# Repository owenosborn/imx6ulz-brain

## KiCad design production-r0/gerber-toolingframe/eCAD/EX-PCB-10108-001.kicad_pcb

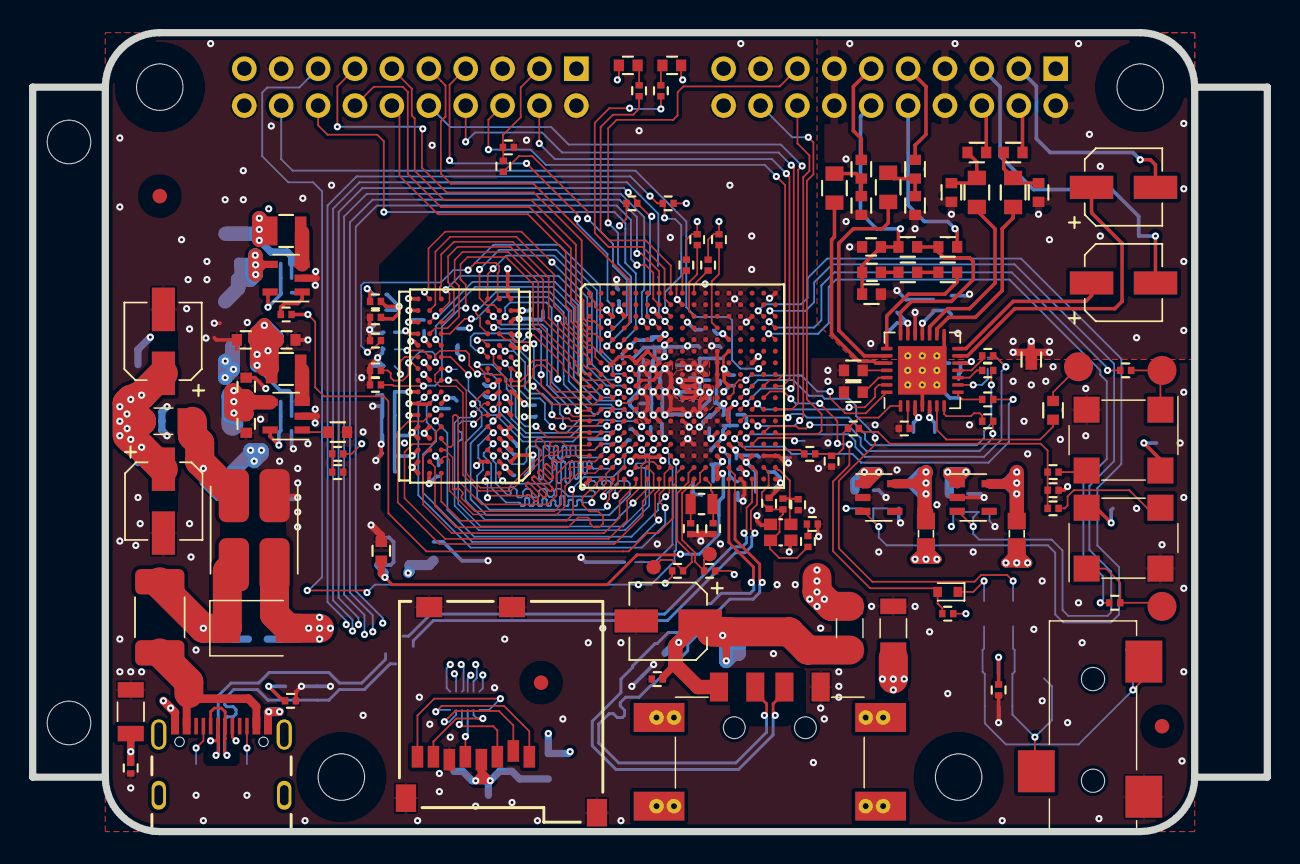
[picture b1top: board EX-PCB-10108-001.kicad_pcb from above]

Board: 4 copper layers, 85.0 x 55.0 mm, 248 parts (0 on the bottom side), 203 nets.

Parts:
C1, C4, C5, C7, C16, C21, C22, C25, C26, C27, C28, C31, C301, C314, C319, C407, C414, C520, C521, C701, C702, C707, C708, C709, C710: PV-EC-CAP-017-22U; 0603
C2, C3, C6, C46, C47: PV-EC-ALU-004-100U; 5.5x5.5x5
C10, C11: PV-EC-CAP-014-8P; 0402
C12, C13, C23, C30, C52, C54, C66, C705, C706: PV-EC-CAP-014-18P; 0402
C14, C15, C24, C302, C303: PV-EC-CAP-010-4U7; 0402
C17: PV-EC-CAP-022-10N; 0603
C18, C19, C65: PV-EC-CAP-022-220N; 0603
C20, C29, C32, C33, C34, C36, C38, C39, C44, C45, C50, C53, C57, C58, C59, C304, C305, C306, C307, C308, C309, C310, C311, C312, C315, C317, C318, C401, C402, C403, C406, C408, C409, C411, C415, C416, C417, C418, C419, C420, C421, C422, C423, C424, C425, C426, C427, C501, C503, C507, C509: PV-EC-CAP-011-220N; 0402
C35, C37, C42, C43, C51, C313, C316: PV-EC-CAP-017-10U; 0603
C40, C41, C48, C49: PV-EC-CAP-029-10U; 0805
C55: PV-EC-CAP-020-1U; 0603
C56: PV-EC-CAP-022-220P; 0603
C62: PV-EC-CAP-034-10N; 1206
C63, C64: PV-EC-CAP-022-1N; 0603
CN1, CN3: PV-EC-CON-008-014; PinHeader_2x10_P2.54mm_Vertical
CN2: PV-EC-CON-013-006; 2908-05WB-MG
CN4: PV-EC-CON-010-010; USB4105-GF-A
CN5: PV-EC-CON-012-003; 35RASMT2BHNTRX
CN6: PV-EC-CON-010-004; 629104190121
D1: PV-EC-OPT-006-003; 0603
D2: PV-EC-OPT-006-002; 0603
D3: PV-EC-DIO-001-001; SOD-523
D4: PV-EC-PTN-003-012; DO-214AA-2
F1: PV-EC-PTN-005-006; 1812
FB1, FB2, FB3, FB4, FB5, FB9: PV-EC-FIL-004-002; 1206
FB6, FB7, FB8, FB10, FB11: PV-EC-FIL-004-001; 0603_FB
FID801, FID802, FID803, FID804, FID805, FID806: PV-EC-BRD-003-001; Fiducial_1mm
L1, L3: PV-EC-FIL-006-002; DLW21H
L2: PV-EC-FIL-006-003; CM2021Y330R-10
L701, L702: PV-EC-IND-010-2U2; 1008
MH1, MH2, MH3, MH4: PV-EC-BRD-007-005; MH_3.2_M3
R1, R2, R5, R9, R11, R13, R14, R23, R49, R50, R51, R52, R53, R54, R57, R504, R508, R509: PV-EC-RES-007-10K; 0402
R3: PV-EC-RES-007-3R3; 0402
R4: PV-EC-RES-010-100K; 0603
R6, R7, R8, R45: PV-EC-RES-007-1M; 0402
R10: PV-EC-RES-007-0R; 0402
R12, R24, R25, R26, R32, R34, R35, R36, R39, R43, R55, R56: PV-EC-RES-007-33R; 0402
R15, R16, R17, R18: PV-EC-RES-010-5K6; 0603
R19, R20, R21, R22, R29, R30, R42: PV-EC-RES-010-47K; 0603
R27, R28, R33: PV-EC-RES-010-100R; 0603
R31, R41: PV-EC-RES-010-0R; 0603
R37, R38: PV-EC-RES-010-150R; 0603
R40: PV-EC-RES-010-680R; 0603
R44, R48: PV-EC-RES-007-1K; 0402
R46, R47: PV-EC-RES-010-5K11; 0603
R58, R59: PV-EC-RES-007-1K5; 0402
R301, R302: PV-EC-RES-007-100K; 0402
R402, R406, R407: PV-EC-RES-007-240R; 0402
R403: PV-EC-RES-007-470R; 0402
R701: PV-EC-RES-007-453K; 0402
R703: PV-EC-RES-007-147K; 0402
TP1, TP3, TP6: PV-EC-BRD-004-1MM; TP_10
TP2, TP4, TP5, TP7, TP8: PV-EC-BRD-004-2MM; TP_20
U1, U4, U504: PV-EC-PWR-008-002; SOT-23-5
U2: PV-EC-PTN-004-004; LLP-2513-13L
U3, U7, U8: PV-EC-PTN-004-001; SOT-23-6
U6: PV-EC-AIC-003-006; QFN-28-5x5-EP
U301: PV-EC-SOC-003-004; MAPBGA-289-14x14
U401: PV-EC-MEM-008-4G; FBGA_96_DDR3L_Combo
U701, U702: PV-EC-PWR-005-001; SOT-23-5
Y1: PV-EC-CLK-003-007; CRY_2x1.6
Y2: PV-EC-CLK-003-004; CRY_2x1.2
Y3: PV-EC-CLK-004-004; OSC_5x7.5x2.5
Y4: PV-EC-CLK-004-005; OSC_5x7.5x2.5

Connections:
+1.5V: C301.1, C303.1, C305.1, C306.1, C402.2, C407.1, C408.1, C409.1, C411.1, C414.1, C415.1, C417.1, C419.1, C420.1, C421.1, C422.1, C423.1, C424.1, C425.1, C426.1, C427.1, C706.1, C708.1, C710.1, L701.2, R59.2, R703.1, U301.G6, U301.H6, U301.H9, U301.H10, U301.J6, U301.J9, U301.J10, U301.K6, U301.K9, U301.K10, U301.L6, U301.M6, U401.A1, U401.A8, U401.B2, U401.C1, U401.C9, U401.D2, U401.D9, U401.E9, U401.F1, U401.G7, U401.H2, U401.H9, U401.K2, U401.K8, U401.N1, U401.N9, U401.R1, U401.R9
+3.3V: C20.1, C29.1, C53.1, C57.1, C302.1, C304.1, C501.1, C503.1, C507.1, C509.1, C705.1, C707.1, C709.1, CN1.1, CN3.1, D1.2, D2.2, FB6.2, FB7.2, FB8.2, L702.2, R1.1, R5.1, R13.1, R14.1, R49.1, R50.1, R51.1, R52.1, R53.1, R54.1, R701.1, U301.C4, U301.E7, U301.E13, U301.F4, U301.F13, U301.H13, U301.J13, U301.L13, U301.M13, U301.N13, Y3.4, Y4.4
+3.3V.LDO1.ISO: C21.1, C35.1, C37.1, C38.1, C39.1, C42.1, C44.1, FB7.1, U1.5, U6.3, U6.5, U6.12
+3.3V.LDO2.ISO: C28.1, C43.1, C45.1, FB8.1, U4.5, U6.18
+3.3V.SNVS: C307.1, C521.1, R23.2, R57.2, U301.P12, U504.5
+5V: C1.1, C2.1, C3.1, C4.1, C5.1, C18.1, C27.1, C33.1, C34.1, C520.1, CN1.19, CN3.19, FB1.1, FB2.1, FB3.1, FB4.1, U1.1, U4.1, U301.T12, U301.U12, U504.1, U504.3
/Block_Diagram/Audio Codec/44k.EN: R43.2, U301.E17
/Block_Diagram/Audio Codec/48k.EN: R35.1, U301.D17
/Block_Diagram/Audio Codec/ADC.IN.L: CN1.11, R17.1
/Block_Diagram/Audio Codec/ADC.IN.R: CN1.9, R15.1
/Block_Diagram/Audio Codec/CSB: R29.1, U6.26
/Block_Diagram/Audio Codec/DAC.OUT.L: CN1.4, R27.2
/Block_Diagram/Audio Codec/DAC.OUT.R: CN1.6, R28.2
/Block_Diagram/Audio Codec/HP.OUT.L: C46.2, CN1.3, R21.1
/Block_Diagram/Audio Codec/HP.OUT.R: C47.2, CN1.5, R19.1
/Block_Diagram/Audio Codec/I2C2.SCL: U6.28, U301.K13
/Block_Diagram/Audio Codec/I2C2.SDA: U6.27, U301.L15
/Block_Diagram/Audio Codec/LHPOUT: C46.1, U6.13
/Block_Diagram/Audio Codec/LLINEIN: C41.1, U6.24
/Block_Diagram/Audio Codec/LOUT: C48.2, U6.16
/Block_Diagram/Audio Codec/MIC.BIAS: CN1.10, R41.2
/Block_Diagram/Audio Codec/MIC.IN: C55.1, C56.1, CN1.12, R40.2, R42.1
/Block_Diagram/Audio Codec/MICBIAS: R40.1, R41.1, U6.21
/Block_Diagram/Audio Codec/MICIN: R37.1, U6.22
/Block_Diagram/Audio Codec/RHPOUT: C47.1, U6.14
/Block_Diagram/Audio Codec/RLINEIN: C40.1, U6.23
/Block_Diagram/Audio Codec/ROUT: C49.2, U6.17
/Block_Diagram/Audio Codec/SAI2.BCK: R26.1, U301.N16
/Block_Diagram/Audio Codec/SAI2.LRCK: R24.1, R32.2, U301.N15
/Block_Diagram/Audio Codec/SAI2.MCLK: C66.1, R55.1, R56.2, U6.1
/Block_Diagram/Audio Codec/SAI2.RXD: R34.2, U301.M14
/Block_Diagram/Audio Codec/SAI2.TXD: R25.1, U301.N14
/Block_Diagram/CPU Periphery I/BM0: R57.1, TP1.1, U301.T10
/Block_Diagram/CPU Periphery I/BM1: R23.1, TP6.1, U301.U10
/Block_Diagram/CPU Periphery I/DBG.RXD: D3.1, FB11.1
/Block_Diagram/CPU Periphery I/DBG.TXD: FB10.1, U301.K14
/Block_Diagram/CPU Periphery I/ECSPI2.CS0: CN3.18, U301.G16
/Block_Diagram/CPU Periphery I/PMIC.ON.REQ: R10.1, U301.T9
/Block_Diagram/CPU Periphery I/UART2.RXD: CN3.6, U301.J16
/Block_Diagram/CPU Periphery I/UART2.TXD: CN3.4, U301.J17
/Block_Diagram/CPU Periphery I/XTALI: C10.1, R6.1, R8.1, U301.T16, Y1.1
/Block_Diagram/CPU Periphery I/XTALO: C11.1, R8.2, U301.T17, Y1.2
/Block_Diagram/CPU Periphery I/~ONOFF: CN3.15, U301.R8
/Block_Diagram/CPU Periphery I/~POR: C14.1, TP3.1, U301.P8
/Block_Diagram/CPU Periphery II/GPIO1: CN1.16, U301.M15
/Block_Diagram/CPU Periphery II/GPIO2: CN1.18, U301.N17
/Block_Diagram/CPU Periphery II/GPIO3: CN1.15, U301.F3
/Block_Diagram/CPU Periphery II/I2C1.SCL: CN3.8, U301.L14
/Block_Diagram/CPU Periphery II/I2C1.SDA: CN3.10, U301.L17
/Block_Diagram/CPU Periphery II/LDO1.EN: R1.2, R2.1, U1.3, U301.C17
/Block_Diagram/CPU Periphery II/LDO2.EN: R5.2, R9.1, U4.3, U301.C16
/Block_Diagram/CPU Periphery II/SAI1.BCK: CN3.7, U301.D3
/Block_Diagram/CPU Periphery II/SAI1.LRCK: CN3.9, U301.D4
/Block_Diagram/CPU Periphery II/SAI1.MCLK: C30.1, CN3.3, R12.2
/Block_Diagram/CPU Periphery II/SAI1.RXD: CN3.13, U301.D2
/Block_Diagram/CPU Periphery II/SAI1.TXD: CN3.11, U301.D1
/Block_Diagram/CPU Periphery II/USB1_N: L3.4, U301.T15
/Block_Diagram/CPU Periphery II/USB1_P: L3.1, U301.U15
/Block_Diagram/CPU Periphery II/USB2_N: L1.4, U301.T13
/Block_Diagram/CPU Periphery II/USB2_P: L1.1, U301.U13
/Block_Diagram/CPU Periphery II/~LED.GREEN: R48.2, U301.B8
/Block_Diagram/CPU Periphery II/~LED.RED: R44.1, U301.A8
/Block_Diagram/CPU Power/NVCC_PLL_OUT: C311.1, C313.1, U301.P13
/Block_Diagram/CPU Power/VDD.HIGH.CAP: C315.1, C316.1, C401.1, U301.N6, U301.R14, U301.R15
/Block_Diagram/CPU Power/VDD_ARM_CAP: C317.1, C318.1, C319.1, U301.G9, U301.G10, U301.G11, U301.H11
/Block_Diagram/CPU Power/VDD_SNVS_CAP: C309.1, U301.N12
/Block_Diagram/CPU Power/VDD_SOC_CAP: C308.1, C310.1, C312.1, C314.1, U301.G8, U301.H8, U301.J8, U301.J11, U301.K8, U301.K11, U301.L8, U301.L9, U301.L10, U301.L11
/Block_Diagram/Connector/5V.F: C19.1, FB1.2, L2.4
/Block_Diagram/Connector/5V.UNF: C65.1, D4.1, F1.1, L2.1
/Block_Diagram/Connector/5V.USBA: C6.1, C7.1, C17.1, C36.1, CN6.1, FB3.2, U3.5
/Block_Diagram/Connector/DBG.RX: C64.1, CN5.4, FB11.2, TP8.1, U8.3, U8.4
/Block_Diagram/Connector/DBG.TX: C63.1, CN5.1, FB10.2, TP7.1, U8.1, U8.6
/Block_Diagram/Connector/GND.UNF: C65.2, CN4.A1B12, CN4.B1A12, D4.2, L2.2
/Block_Diagram/Connector/SD2.CLK: C23.2, R3.2, U2.4
/Block_Diagram/Connector/SD2.CMD: R54.2, U2.3, U301.C8
/Block_Diagram/Connector/SD2.D0: R53.2, U2.5, U301.D7
/Block_Diagram/Connector/SD2.D1: U2.6, U301.B7
/Block_Diagram/Connector/SD2.D2: U2.1, U301.A7
/Block_Diagram/Connector/SD2.D3: U2.2, U301.D6
/Block_Diagram/Connector/SD.VCC: C24.1, C25.1, C26.1, CN2.P4, FB6.1
/Block_Diagram/Connector/USB1F_N: CN4.A7, CN4.B7, L3.3, U7.3, U7.4
/Block_Diagram/Connector/USB1F_P: CN4.A6, CN4.B6, L3.2, U7.1, U7.6
/Block_Diagram/Connector/USB2F_N: CN6.2, L1.3, U3.1, U3.6
/Block_Diagram/Connector/USB2F_P: CN6.3, L1.2, U3.3, U3.4
/Block_Diagram/DRAM/DRAM_ADDR0: U301.L5, U401.N3
/Block_Diagram/DRAM/DRAM_ADDR1: U301.H2, U401.P7
/Block_Diagram/DRAM/DRAM_ADDR2: U301.K1, U401.P3
/Block_Diagram/DRAM/DRAM_ADDR3: U301.M2, U401.N2
/Block_Diagram/DRAM/DRAM_ADDR4: U301.K4, U401.P8
/Block_Diagram/DRAM/DRAM_ADDR5: U301.L1, U401.P2
/Block_Diagram/DRAM/DRAM_ADDR6: U301.G2, U401.R8
/Block_Diagram/DRAM/DRAM_ADDR7: U301.H4, U401.R2
/Block_Diagram/DRAM/DRAM_ADDR8: U301.J4, U401.T8
/Block_Diagram/DRAM/DRAM_ADDR9: U301.L2, U401.R3
/Block_Diagram/DRAM/DRAM_ADDR10: U301.M4, U401.L7
/Block_Diagram/DRAM/DRAM_ADDR11: U301.K3, U401.R7
/Block_Diagram/DRAM/DRAM_ADDR12: U301.L4, U401.N7
/Block_Diagram/DRAM/DRAM_ADDR13: U301.H3, U401.T3
/Block_Diagram/DRAM/DRAM_ADDR14: U301.G1, U401.T7
/Block_Diagram/DRAM/DRAM_ADDR15: U301.K5, U401.M7
/Block_Diagram/DRAM/DRAM_CAS_B: U301.J2, U401.K3
/Block_Diagram/DRAM/DRAM_CS0_B: U301.N2, U401.L2
/Block_Diagram/DRAM/DRAM_CS1_B: U301.H5, U401.L1
/Block_Diagram/DRAM/DRAM_DATA0: U301.T4, U401.E3
/Block_Diagram/DRAM/DRAM_DATA1: U301.U6, U401.H3
/Block_Diagram/DRAM/DRAM_DATA2: U301.T6, U401.F8
/Block_Diagram/DRAM/DRAM_DATA3: U301.U7, U401.H7
/Block_Diagram/DRAM/DRAM_DATA4: U301.U8, U401.F7
/Block_Diagram/DRAM/DRAM_DATA5: U301.T8, U401.H8
/Block_Diagram/DRAM/DRAM_DATA6: U301.T5, U401.G2
/Block_Diagram/DRAM/DRAM_DATA7: U301.U4, U401.F2
/Block_Diagram/DRAM/DRAM_DATA8: U301.U2, U401.B8
/Block_Diagram/DRAM/DRAM_DATA9: U301.U3, U401.C3
/Block_Diagram/DRAM/DRAM_DATA10: U301.U5, U401.C8
/Block_Diagram/DRAM/DRAM_DATA11: U301.R4, U401.A2
/Block_Diagram/DRAM/DRAM_DATA12: U301.P5, U401.A7
/Block_Diagram/DRAM/DRAM_DATA13: U301.P3, U401.C2
/Block_Diagram/DRAM/DRAM_DATA14: U301.R2, U401.D7
/Block_Diagram/DRAM/DRAM_DATA15: U301.R1, U401.A3
/Block_Diagram/DRAM/DRAM_DQM0: U301.T7, U401.E7
/Block_Diagram/DRAM/DRAM_DQM1: U301.T3, U401.D3
/Block_Diagram/DRAM/DRAM_ODT0: U301.N1, U401.K1
/Block_Diagram/DRAM/DRAM_ODT1: U301.F1, U401.J1
/Block_Diagram/DRAM/DRAM_RAS_B: U301.M5, U401.J3
/Block_Diagram/DRAM/DRAM_RESET_B: R509.2, U301.G4, U401.T2
/Block_Diagram/DRAM/DRAM_SDBA0: U301.M1, U401.M2
/Block_Diagram/DRAM/DRAM_SDBA1: U301.H1, U401.N8
/Block_Diagram/DRAM/DRAM_SDBA2: U301.K2, U401.M3
/Block_Diagram/DRAM/DRAM_SDCKE0: R508.1, U301.M3, U401.K9
/Block_Diagram/DRAM/DRAM_SDCKE1: R504.1, U301.J3, U401.J9
/Block_Diagram/DRAM/DRAM_SDCLK0_N: R403.2, U301.P2, U401.K7
/Block_Diagram/DRAM/DRAM_SDCLK0_P: R403.1, U301.P1, U401.J7
/Block_Diagram/DRAM/DRAM_SDQS0_N: U301.P7, U401.G3
/Block_Diagram/DRAM/DRAM_SDQS0_P: U301.P6, U401.F3
/Block_Diagram/DRAM/DRAM_SDQS1_N: U301.T2, U401.B7
/Block_Diagram/DRAM/DRAM_SDQS1_P: U301.T1, U401.C7
/Block_Diagram/DRAM/DRAM_SDWE_B: U301.J1, U401.L3
/Block_Diagram/DRAM/DRAM_VREF: C402.1, C403.1, C406.1, C416.1, C418.1, R58.1, R59.1, U301.P4, U401.H1, U401.M8
/Block_Diagram/DRAM/DRAM_ZQ0: R407.2, U401.L8
/Block_Diagram/DRAM/DRAM_ZQ1: R406.2, U401.L9
/Block_Diagram/DRAM/ZQPAD: R402.2, U301.N4
/Block_Diagram/ECSPI2.MISO: CN3.12, U301.E1
/Block_Diagram/ECSPI2.MOSI: CN3.14, U301.E2
/Block_Diagram/ECSPI2.SCK: CN3.16, U301.E4
GND: C1.2, C2.2, C3.2, C4.2, C5.2, C6.2, C7.2, C10.2, C11.2, C12.2, C13.2, C14.2, C15.2, C16.2, C17.2, C18.2, C19.2, C20.2, C21.2, C22.2, C23.1, C24.2, C25.2, C26.2, C27.2, C28.2, C29.2, C30.2, C31.2, C32.2, C33.2, C34.2, C35.2, C36.2, C37.2, C38.2, C39.2, C42.2, C44.2, C52.1, C53.2, C54.1, C57.2, C58.2, C59.2, C62.2, C63.2, C64.2, C66.2, C301.2, C302.2, C303.2, C304.2, C305.2, C306.2, C307.2, C308.2, C309.2, C310.2, C311.2, C312.2, C313.2, C314.2, C315.2, C316.2, C317.2, C318.2, C319.2, C401.2, C403.2, C406.2, C407.2, C408.2, C409.2, C411.2, C414.2, C415.2, C416.2, C417.2, C418.2, C419.2, C420.2, C421.2, C422.2, C423.2, C424.2, C425.2, C426.2, C427.2, C501.2, C503.2, C507.2, C509.2, C520.2, C521.2, C701.2, C702.2, C707.2, C708.2, C709.2, C710.2, CN1.17, CN1.20, CN2.G1, CN2.G2, CN2.G3, CN2.G4, CN2.P6, CN3.2, CN3.5, CN3.17, CN3.20, CN5.5, CN6.4, FB5.2, FB9.2, L2.3, R2.2, R4.2, R7.2, R9.2, R11.1, R29.2, R30.2, R31.1, R45.2, R46.2, R47.2, R58.2, R301.2, R302.2, R402.1, R406.1, R407.1, R504.2, R508.2, R509.1, U1.2, U2.13, U3.2, U4.2, U6.4, U6.15, U6.EP, U7.2, U8.2, U301.A1, U301.A11, U301.A12, U301.A13, U301.A14, U301.A17, U301.B9, U301.B10, U301.B11, U301.B12, U301.B13, U301.B14, U301.B16, U301.C3, U301.C7, U301.C11, U301.C12, U301.C13, U301.C14, U301.C15, U301.D10, U301.D11, U301.D13, U301.D14, U301.E8, U301.E10, U301.E11, U301.E12, U301.F6, U301.F7, U301.F8, U301.F9, U301.F10, U301.F11, U301.F12, U301.G3, U301.G5, U301.G7, U301.G12, U301.G15, U301.H7, U301.H12, U301.J5, U301.J7, U301.J12, U301.K7, U301.K12, U301.L3, U301.L7, U301.L12, U301.M7, U301.M8, U301.M9, U301.M10, U301.M11, U301.M12, U301.N3, U301.N5, U301.N7, U301.N8, U301.N9, U301.N10, U301.N11, U301.P9, U301.P10, U301.P11, U301.R3, U301.R5, U301.R6, U301.R7, U301.R9, U301.R10, U301.R11, U301.R16, U301.R17, U301.T14, U301.U1, U301.U14, U301.U17, U401.A9, U401.B1, U401.B3, U401.B9, U401.D1, U401.D8, U401.E1, U401.E2, U401.E8, U401.F9, U401.G1, U401.G8, U401.G9, U401.J2, U401.J8, U401.M1, U401.M9, U401.P1, U401.P9, U401.T1, U401.T9, U504.2, U701.2, U702.2, Y1.G, Y3.2, Y4.2
GNDA: C43.2, C45.2, C50.2, C51.2, C56.2, CN1.2, CN1.7, CN1.8, CN1.13, CN1.14, R16.2, R18.2, R19.2, R20.2, R21.2, R22.2, R31.2, R42.2, U6.19
unnamed: C12.1, U301.T11, Y2.1
unnamed: C13.1, U301.U11, Y2.2
unnamed: C15.1, R4.1, R14.2, U702.1
unnamed: C16.1, C701.1, FB2.2, U701.4
unnamed: C22.1, C702.1, FB4.2, U702.4
unnamed: C31.1, C32.1, U301.R12
unnamed: C40.2, R15.2, R16.1
unnamed: C41.2, R17.2, R18.1
unnamed: C48.1, R22.1, R27.1
unnamed: C49.1, R20.1, R28.1
unnamed: C50.1, C51.1, U6.20
unnamed: C52.2, U6.2
unnamed: C54.2, R36.2, R39.1, R55.2
unnamed: C55.2, R38.2
unnamed: C58.1, U7.5
unnamed: C59.1, U8.5
unnamed: C62.1, CN4.SH, FB9.1, R45.1
unnamed: C705.2, R301.1, R701.2, U701.5
unnamed: C706.2, R302.1, R703.2, U702.5
unnamed: CN2.P1, U2.12
unnamed: CN2.P2, U2.11
unnamed: CN2.P3, U2.10
unnamed: CN2.P5, U2.9
unnamed: CN2.P7, U2.8
unnamed: CN2.P8, U2.7
unnamed: CN4.A4B9, CN4.B4A9, F1.2
unnamed: CN4.A5, R46.1
unnamed: CN4.B5, R47.1
unnamed: CN6.SH, FB5.1
unnamed: D1.1, R48.1
unnamed: D2.1, R44.2
unnamed: D3.2, R13.2, U301.K16
unnamed: L701.1, U702.3
unnamed: L702.1, U701.3
unnamed: R3.1, U301.D8
unnamed: R6.2, R7.1
unnamed: R10.2, U701.1
unnamed: R11.2, U301.P15
unnamed: R12.1, U301.E3
unnamed: R24.2, U6.9
unnamed: R25.2, U6.8
unnamed: R26.2, U6.7
unnamed: R30.1, U6.25
unnamed: R32.1, U6.11
unnamed: R33.1, U6.6
unnamed: R33.2, TP2.1
unnamed: R34.1, U6.10
unnamed: R35.2, TP4.1, Y3.1
unnamed: R36.1, Y3.3
unnamed: R37.2, R38.1
unnamed: R39.2, Y4.3
unnamed: R43.1, TP5.1, Y4.1
unnamed: R49.2, U301.A9
unnamed: R50.2, U301.C10
unnamed: R51.2, U301.A10
unnamed: R52.2, U301.D12
unnamed: R56.1, U301.P14

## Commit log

2022-12-26 initial commit, r0
2022-12-26 add power path header
2022-12-26 adding old order files
2022-12-26 routed power path controller
2022-12-27 r1 cam files
2023-01-02 touch up sch
2023-01-16 stencil for r1
